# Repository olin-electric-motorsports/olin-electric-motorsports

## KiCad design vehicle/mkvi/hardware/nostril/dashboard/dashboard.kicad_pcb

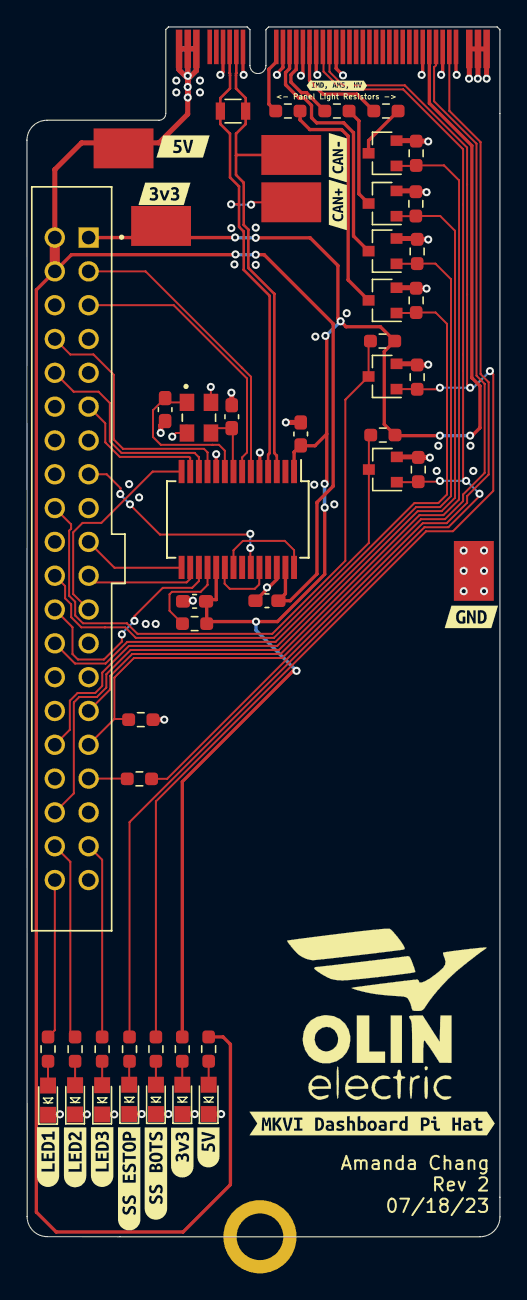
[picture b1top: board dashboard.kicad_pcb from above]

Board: 2 copper layers, 35.5 x 90.9 mm, 64 parts (0 on the bottom side), 48 nets.

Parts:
C4, C5, C6: C_0.1uF; C_0603_1608Metric_Pad1.08x0.95mm_HandSolder
C7, C8: C_14pF; C_0603_1608Metric_Pad1.08x0.95mm_HandSolder
D1, D7: LED_BLUE; LED_0805_OEM
D2, D3, D4, D5, D6: LED_0805; LED_0805_OEM
H1: M.2_MountingHole; M.2_Mount
J2: Automotive_M.2_Edge_Connector
J101: Conn_02x20_Odd_Even; SULLINS_SFH11-PBPC-D20-ST-BK
Q1, Q2, Q3, Q4, Q5, Q6: SSM3K333R; SOT-23F
R1, R7, R10, R16, R17, R18, R19, R20, R21: R_1K; R_0603_1608Metric_Pad0.98x0.95mm_HandSolder
R2, R12: R_100K; R_0603_1608Metric_Pad0.98x0.95mm_HandSolder
R3, R13, R14, R15: R_10K; R_0603_1608Metric_Pad0.98x0.95mm_HandSolder
R4, R5, R6, R8, R9, R11: R_200; R_0603_1608Metric_Pad0.98x0.95mm_HandSolder
R22: R_120_DNP; R_0805_OEM
TP1, TP2, TP3, TP4, TP5: Test_Point_SMD
U2: MCP25625-x-SS; SSOP-28_5.3x10.2mm_P0.65mm
Y1: Crystal_8MHz_12pF; XTAL_ECS-240-8-33-AGN-TR
kibuzzard-63A7A1A6: G***; kibuzzard-63A7A1A6
kibuzzard-63A7A1B1: G***; kibuzzard-63A7A1B1
kibuzzard-63A7A2B8: G***; kibuzzard-63A7A2B8
kibuzzard-63A7A2BB: G***; kibuzzard-63A7A2BB
kibuzzard-63A7A2C4: G***; kibuzzard-63A7A2C4
kibuzzard-63A7A2C6: G***; kibuzzard-63A7A2C6
kibuzzard-63A7A2C9: G***; kibuzzard-63A7A2C9
kibuzzard-63A7A2CE: G***; kibuzzard-63A7A2CE
kibuzzard-63A7A2D2: G***; kibuzzard-63A7A2D2
kibuzzard-63B4F55C: G***; kibuzzard-63B4F55C
kibuzzard-63B4F247: G***; kibuzzard-63B4F247
kibuzzard-63B43D68: G***; kibuzzard-63B43D68
kibuzzard-63B49D83: G***; kibuzzard-63B49D83
kibuzzard-63B49DDB: G***; kibuzzard-63B49DDB

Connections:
+3V3: C4.1, C5.1, J2.33, J101.1, R3.1, R5.1, R13.2, R14.1, TP3.1, U2.1 (VIO), U2.19 (VDD)
+5V: C6.2, J2.P1, J2.P2, J2.P3, J101.2, J101.4, R4.1, TP2.1, U2.27 (VDDA)
/AMS_LED_LOW_SIDE: J2.13, R20.1
/AMS_LED_LSD: J101.36, Q3.1 (G), R16.1
/BOTS_SHDN_SENSE: J101.18, Q6.3 (D), R3.2
/CAN_+: J2.7, R22.1, TP4.1, U2.4 (CANH)
/CAN_-: J2.8, R22.2, TP5.1, U2.3 (CANL)
/E_STOP_SHDN_SENSE: J101.22, Q1.3 (D), R14.2
/HV_LED_LOW_SIDE: J2.15, R21.1
/HV_LED_LSD: J101.29, Q5.1 (G), R18.1
/IMD_LED_LOW_SIDE: J2.10, R19.1
/IMD_LED_LSD: J101.26, Q2.1 (G), R10.1
/MCP25625 Chip/RX_CAN: U2.21 (RxCAN), U2.28 (RXD)
/MCP25625 Chip/TX_CAN: U2.20 (TxCAN), U2.24 (TXD)
/MCP25625 Chip/~INT: J101.11, U2.13 (~INT)
/MCP25625 Chip/~RESET: R13.1, U2.18 (~RESET)
/MCP25625 Chip/~TX1RTS: J101.3, U2.6 (~Tx1RTS)
/MCP25625 Chip/~TX2RTS: J101.5, U2.7 (~Tx2RTS)
/MISO: J101.21, U2.16 (SO)
/MOSI: J101.19, U2.15 (SI)
/PROGRAMMING_LED_1: J101.40, R6.1
/PROGRAMMING_LED_2: J101.38, R8.1
/PROGRAMMING_LED_3: J101.37, R9.1
/RTD_BUTTON_LED+: J101.33, R11.1
/RTD_BUTTON_SENSE-: J2.34, J101.31, R15.1
/RTD_BUZZER_LOW_SIDE: J2.12, Q4.3 (D)
/RTD_BUZZER_LSD: J101.32, Q4.1 (G), R17.1
/SCK: J101.23, U2.14 (SCK)
/SS_BOTS: J2.18, Q6.1 (G), R1.1, R2.1
/SS_ESTOP_DRIVER: J2.17, Q1.1 (G), R7.1, R12.1
/~CS: J101.24, U2.17 (~CS)
/~RX0BF: J101.10, U2.12 (~Rx0BF)
/~RX1BF: J101.8, U2.11 (~Rx1BF)
/~TX0RTS: J101.15, U2.23 (~Tx0RTS)
GND: C4.2, C5.2, C6.1, C7.2, C8.2, D1.1 (K), D2.1 (K), D3.1 (K), D4.1 (K), D5.1 (K), D6.1 (K), D7.1 (K), H1.1, J2.6, J2.9, J2.11, J2.14, J2.16, J2.19, J2.32, J2.35, J2.37, J2.P38, J2.P39, J2.P40, J101.6, J101.9, J101.14, J101.20, J101.25, J101.30, J101.34, J101.39, Q1.2 (S), Q2.2 (S), Q3.2 (S), Q4.2 (S), Q5.2 (S), Q6.2 (S), R2.2, R10.2, R12.2, R15.2, R16.2, R17.2, R18.2, TP1.1, U2.5 (STBY), U2.10 (GND), U2.26 (VSS), Y1.2, Y1.4
unnamed: D1.2 (A), R1.2
unnamed: D2.2 (A), R4.2
unnamed: D3.2 (A), R5.2
unnamed: D4.2 (A), R6.2
unnamed: D5.2 (A), R8.2
unnamed: D6.2 (A), R9.2
unnamed: D7.2 (A), R7.2
unnamed: J2.36, R11.2
unnamed: Q2.3 (D), R19.2
unnamed: Q3.3 (D), R20.2
unnamed: Q5.3 (D), R21.2
unnamed: C7.1, U2.9 (OSC1), Y1.1
unnamed: C8.1, U2.8 (OSC2), Y1.3

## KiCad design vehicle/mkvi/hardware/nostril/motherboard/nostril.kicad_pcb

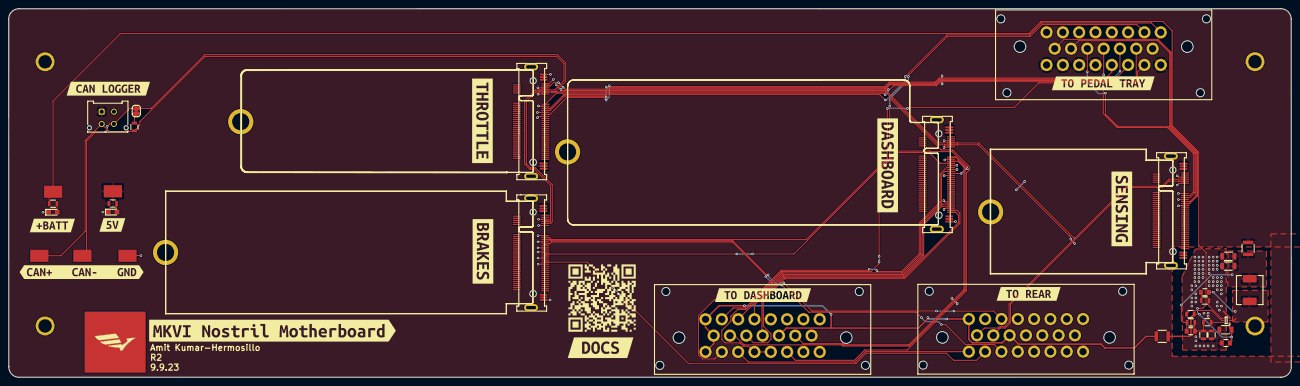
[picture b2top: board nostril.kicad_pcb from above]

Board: 2 copper layers, 314.4 x 90.3 mm, 53 parts (0 on the bottom side), 40 nets.

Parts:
C1: C_0.1uF; C_0805_OEM
C2, C5, C6: C_22uF; C_1206_OEM
C3: C_1uF; C_0805_OEM
C4: 15pF; C_0805_OEM
D1, D2: LED_WHITE; CHIPLED_0805
F1, F2: F_500mA_16V; Fuse_1210
J1, J2, J3: Ampseal_23_RA
J4, J5, J6, J7: Automotive_M.2
J8: MicroFit_VT_4
JP1: SolderJumper_2_Open; SolderJumper-2_P1.3mm_Open_RoundedPad1.0x1.5mm
L1: 2.2uH; IND_SPM6530T-2R2M
QR*****: https://coda.io/d/Documentation_dbuFnC2EA_e/Low-V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; __coda.io_d_Documentation_dbuFnC2EA_e_Low-Voltage-Syste
R1, R8: R_200; R_0805_OEM
R2: R_100K; R_0805_OEM
R3: 10R; R_0805_OEM
R4: R_75k; R_0805_OEM
R5: R_10K; R_0805_OEM
R6: R_33.2k; R_0805_OEM
R7: 40.2K; R_0805_OEM
R9: R_120_DNP; R_0805_OEM
REFe: MountingHole_440_Keystone_4939
REFe#2, REFe#3, REFe#4: MountingHole_440_Keystone_4939
TP1, TP2, TP3, TP4, TP5: Test_Point_SMD
U1: MP1477HGTF-P; SOTFL50P160X60-6N
kibuzzard-63FE4A40: G***; kibuzzard-63FE4A40
kibuzzard-63FE5D89: G***; kibuzzard-63FE5D89
kibuzzard-63FE5E2A: G***; kibuzzard-63FE5E2A
kibuzzard-63FE5E61: G***; kibuzzard-63FE5E61
kibuzzard-63FE5E77: G***; kibuzzard-63FE5E77
kibuzzard-63FE47A2: G***; kibuzzard-63FE47A2
kibuzzard-63FE47AC: G***; kibuzzard-63FE47AC
kibuzzard-63FE478D: G***; kibuzzard-63FE478D
kibuzzard-63FE479B: G***; kibuzzard-63FE479B
kibuzzard-63FE2233: G***; kibuzzard-63FE2233
kibuzzard-63FE2239: G***; kibuzzard-63FE2239
kibuzzard-63FE2383: G***; kibuzzard-63FE2383
kibuzzard-63FF646A: G***; kibuzzard-63FF646A

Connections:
+5V: F2.2, J3.1, J3.5, J3.6, J3.7, J3.8, J4.P1, J4.P2, J4.P3, J5.P38, J5.P39, J5.P40, J6.P1, J6.P2, J6.P3, J7.P1, J8.1, R8.2, TP4.1
+BATT: F1.1, J1.1, J1.9, J1.13, J1.16, J2.1, J2.11
/5V Buck/BUCK_EN: R2.2, U1.5 (EN)
/AMS_LED-: J1.2, J4.13
/BRAKELIGHT-: J2.18, J6.14, J6.15
/BRAKE_PRESSURE_SENSE: J3.2, J6.11
/CAN_+: J2.9, J4.7, J5.7, J6.7, J7.7, J8.3, R9.1, TP1.1
/CAN_-: J2.10, J4.8, J5.8, J6.8, J7.8, J8.4, JP1.2 (B), TP2.1
/IMD_LED-: J1.10, J4.10
/INPUT_THROTTLE_1: J3.10, J5.10
/INPUT_THROTTLE_2: J3.11, J5.5
/MOTOR_CURRENT_SENSE: J2.3, J6.12
/RTD_BUTTON_SENSE+: J1.3, J4.33
/RTD_BUTTON_SENSE-: J1.4, J4.34
/RTD_BUZZER-: J1.14, J4.12
/RTD_LED+: J1.11, J4.36
/RTD_LED-: J1.12, J4.37
/SHDN_BOTS_IN: J3.17, J4.18, J6.19, J6.20
/SHDN_BOTS_OUT: J1.21, J3.16, J5.12
/SHDN_ESTOP_IN: J1.19, J1.20, J4.17
/SHDN_ESTOP_OUT: J1.18, J2.16
/SHDN_OUT: J2.17, J6.22, J6.23
/SUS_TRAVEL_L_SIG: J3.14, J7.14
/SUS_TRAVEL_R_SIG: J3.15, J7.15
/THROTTLE_1+: J3.3, J5.13
/THROTTLE_2+: J3.4, J5.15
/TS_LED-: J1.17, J4.15
/WHEEL_SPEED_L_SIG: J3.12, J7.11
/WHEEL_SPEED_R_SIG: J3.13, J7.12
GND: C1.2, C2.2, C5.2, C6.2, D1.1 (K), D2.1 (K), J2.2, J3.9, J3.18, J3.19, J3.20, J3.21, J3.22, J3.23, J4.6, J4.9, J4.11, J4.14, J4.16, J4.19, J4.32, J4.35, J4.P38, J4.P39, J4.P40, J5.4, J5.6, J5.9, J5.11, J5.14, J5.16, J5.P1, J5.P2, J5.P3, J6.6, J6.9, J6.10, J6.13, J6.16, J6.18, J6.21, J6.24, J6.P38, J6.P39, J6.P40, J7.6, J7.9, J7.10, J7.13, J7.16, J8.2, R5.2, R6.2, REFe.1, REFe#2.1, REFe#3.1, REFe#4.1, TP5.1, U1.3 (GND)
unnamed: C3.1, R3.2
unnamed: C4.1, R4.2, R5.1, R6.1, R7.1
unnamed: C4.2, C5.1, C6.1, F2.1, L1.2, R7.2
unnamed: D1.2 (A), R1.1
unnamed: D2.2 (A), R8.1
unnamed: JP1.1 (A), R9.2
unnamed: R3.1, U1.4 (BST)
unnamed: R4.1, U1.6 (FB)
unnamed: C3.2, L1.1, U1.2 (SW)
unnamed: C1.1, C2.1, F1.2, R1.2, R2.1, TP3.1, U1.1 (VIN)

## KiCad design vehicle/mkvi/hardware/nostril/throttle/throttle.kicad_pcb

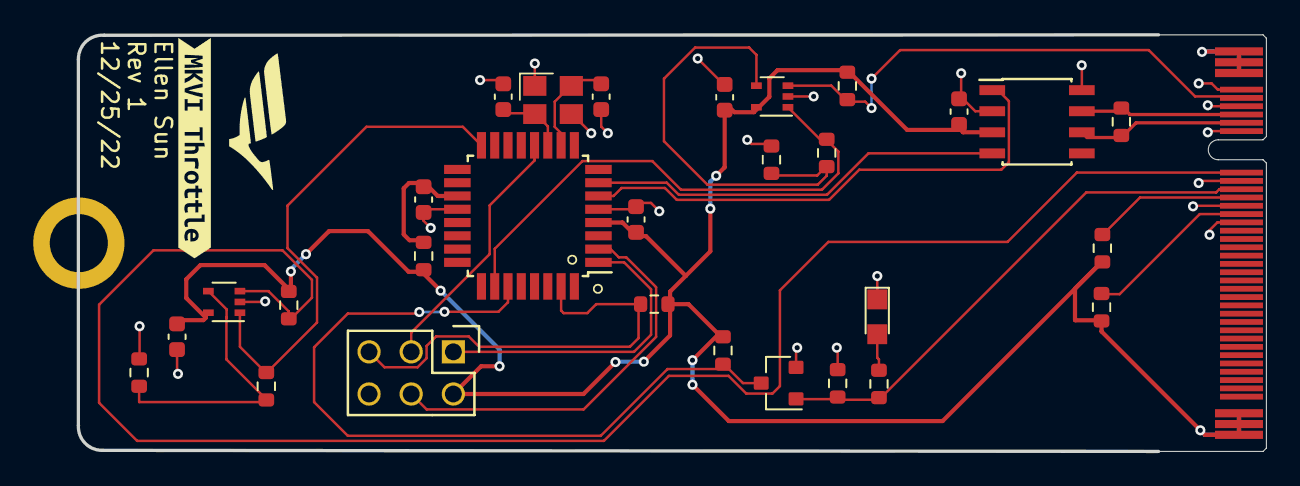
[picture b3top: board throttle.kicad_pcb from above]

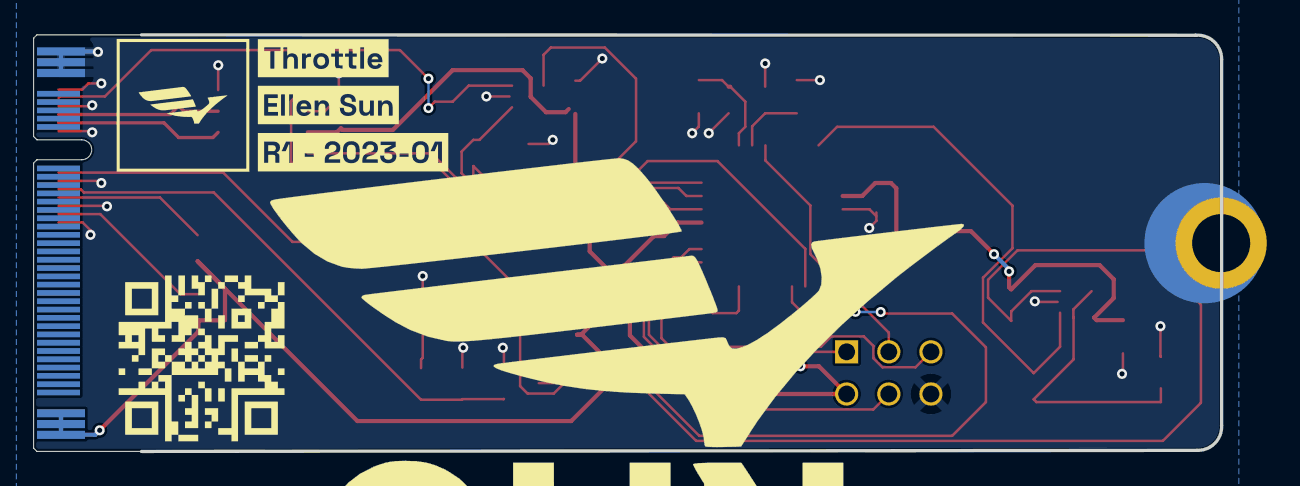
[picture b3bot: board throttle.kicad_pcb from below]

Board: 2 copper layers, 71.6 x 25.1 mm, 36 parts (4 on the bottom side), 24 nets.

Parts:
C1, C2, C3, C7: 0.1uF; C_0603
C4: C_100pF; C_0603
C5, C6: C_30pF; C_0603
D1: LED_BLUE; CHIPLED_0805
J1: Automotive_M.2_Edge_Connector
J2: CONN_02x03; Pin_Header_Straight_2x03
Q1: SSM3K333R; SOT-23F
QR*****: hw.oem.to/6_THROTTLE_1; QR_6_THROTTLE_1
R1, R4: R_1M; R_0603
R2, R5, R10, R11: R_0; R_0603
R3, R6: R_2.2K; R_0603
R7: 3KR; R_0603
R8: R_100K; R_0603
R9, R13: R_10K; R_0603
R12: R_100; R_0603
R14: R_120_DNP; R_0603
U1, U2: MCP6001; SOT-353_SC-70-5
U3: ATMEGA16M1; TQFP-32_7x7mm_Pitch0.8mm
U4: MAX33011EASA; SOIC-8_3.9x4.9mm_Pitch1.27mm_OEM
U$2: M.2_Mount
Y1: Crystal_16MHz_18pF; Crystal_TXC7M
kibuzzard-63A88E8E: G***; kibuzzard-63A88E8E
kibuzzard-63BF4696: G***; kibuzzard-63BF4696
kibuzzard-63D83A03: G***; kibuzzard-63D83A03
kibuzzard-63D83A10: G***; kibuzzard-63D83A10

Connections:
+5V: C1.1, C2.1, C3.1, C7.1, J1.P38, J1.P39, J1.P40, J2.2, R1.1, R4.1, R9.1, R10.1, R11.1, R12.1, R13.1, U1.5 (V+), U2.5 (V+), U3.4 (VCC), U4.3 (VDD)
/ Shutdown Sense Inertial Switch/SS_INERTIA_OUTPUT: Q1.3 (D), R9.2, U3.27 ((PCINT6/ADC7/PSCOUT1B)PB6)
/CAN_+: J1.7, R14.1, U4.7 (CANH)
/CAN_-: J1.8, R14.2, U4.6 (CANL)
/INPUT_THROTTLE_1: J1.10, R1.2, U1.3 (+)
/INPUT_THROTTLE_2: J1.5, R4.2, U2.3 (+)
/Microcontroller/CAN_RX: U3.7 ((PCINT11/T1/ICP1B/RXCAN)PC3), U4.4 (RXD)
/Microcontroller/CAN_TX: U3.6 ((PCINT10/T0/TXCAN)PC2), U4.1 (TXD)
/Microcontroller/MISO: J2.1, U3.1 ((PCINT18/PSCIN2/OC1A/MISO_A)PD2)
/Microcontroller/MOSI: J2.4, U3.2 ((PCINT19/TXD/TXLIN/OC0A/~SS/MOSI_A)PD3)
/Microcontroller/OUTPUT_THROTTLE_1: R2.1, U1.1, U3.16 ((PCINT2/ADC5/INT1/ACMPN0)PB2)
/Microcontroller/OUTPUT_THROTTLE_2: R5.1, U2.1, U3.26 ((PCINT5/ADC6/INT2/ACMPN1/AMP2-)PB5)
/Microcontroller/RESET: J2.5, R13.2, U3.31 ((PCINT24/OCD/~RESET)PE0)
/Microcontroller/SCK: J2.3, U3.12 ((PCINT20/ADC1/RXD/RXLIN/ICP1A/SCK_A)PD4)
/SS_INERTIA_SWITCH: J1.12, Q1.1 (G), R7.2, R8.1
/THROTTLE_1+: J1.13, R10.2
/THROTTLE_2+: J1.15, R11.2
GND: C1.2, C2.2, C3.2, C4.2, C5.2, C6.2, C7.2, D1.1 (K), J1.4, J1.6, J1.9, J1.11, J1.14, J1.16, J1.P1, J1.P2, J1.P3, J2.6, Q1.2 (S), R3.2, R6.2, R8.2, U1.2 (V-), U2.2 (V-), U3.5 (GND), U3.20 (AGND), U4.2 (VSS), U4.8 (STBY), U$2.1, Y1.2, Y1.4
unnamed: C4.1, R12.2, U3.19 (AVCC)
unnamed: C5.1, U3.11 ((PCINT26/ADC0/XTAL2)PE2), Y1.1
unnamed: C6.1, U3.10 ((PCINT25/OC0B/XTAL1)PE1), Y1.3
unnamed: D1.2 (A), R7.1
unnamed: R2.2, R3.1, U1.4 (-)
unnamed: R5.2, R6.1, U2.4 (-)

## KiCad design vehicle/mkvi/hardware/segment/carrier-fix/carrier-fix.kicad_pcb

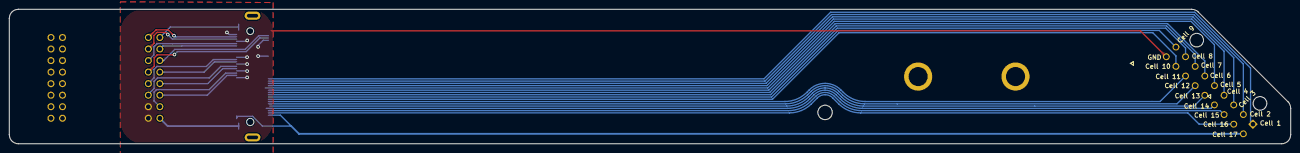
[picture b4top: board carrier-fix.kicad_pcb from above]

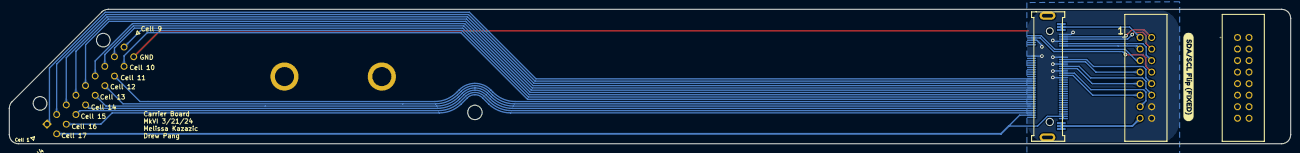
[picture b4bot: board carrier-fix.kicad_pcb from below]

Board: 2 copper layers, 282.1 x 29.6 mm, 6 parts (6 on the bottom side), 32 nets.

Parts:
J1: Automotive_M.2; MKVI_BMS_CSC
J2, J3: TST-108-01-T-D; TST-108-XX-T-D
J4, J4#2: MicroFit_RA_9x2
kibuzzard-65FD0D90: G***; kibuzzard-65FD0D90

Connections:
/CELL1: J1.56, J4.1
/CELL2: J1.57, J4.2
/CELL3: J1.58, J4.3
/CELL4: J1.59, J4.4
/CELL5: J1.60, J4.5
/CELL6: J1.61, J4.6
/CELL7: J1.62, J4.7
/CELL8: J1.63, J4.8
/CELL9: J1.64, J4.9
/CELL10: J1.65, J4.17
/CELL11: J1.66, J4.16
/CELL12: J1.67, J4.15
/CELL13: J1.68, J4.14
/CELL14: J1.69, J4.13
/CELL15: J1.70, J4.12
/CELL16: J1.71, J4.11
/CELL17: J1.36, J1.37, J1.72, J4.10
/GND: J1.4, J1.7, J1.10, J1.13, J1.16, J1.19, J1.43, J1.46, J2.14, J2.16, J4.18
/MUX1_SC: J1.18, J2.11
/MUX1_SD: J1.17, J2.13
/MUX2_SC: J1.15, J2.9
/MUX2_SD: J1.14, J2.12
/MUX3_SC: J1.12, J2.7
/MUX3_SD: J1.11, J2.10
/MUX4_SC: J1.9, J2.3
/MUX4_SD: J1.8, J2.6
/MUX_OUT_1: J1.6, J2.4
/MUX_OUT_2: J1.42, J2.8
/MUX_OUT_3: J1.5, J2.2
/MUX_OUT_4: J1.41, J2.5
/VREF2: J1.P38, J1.P39, J1.P40, J2.15
/VREG: J1.P1, J1.P2, J1.P3, J2.1

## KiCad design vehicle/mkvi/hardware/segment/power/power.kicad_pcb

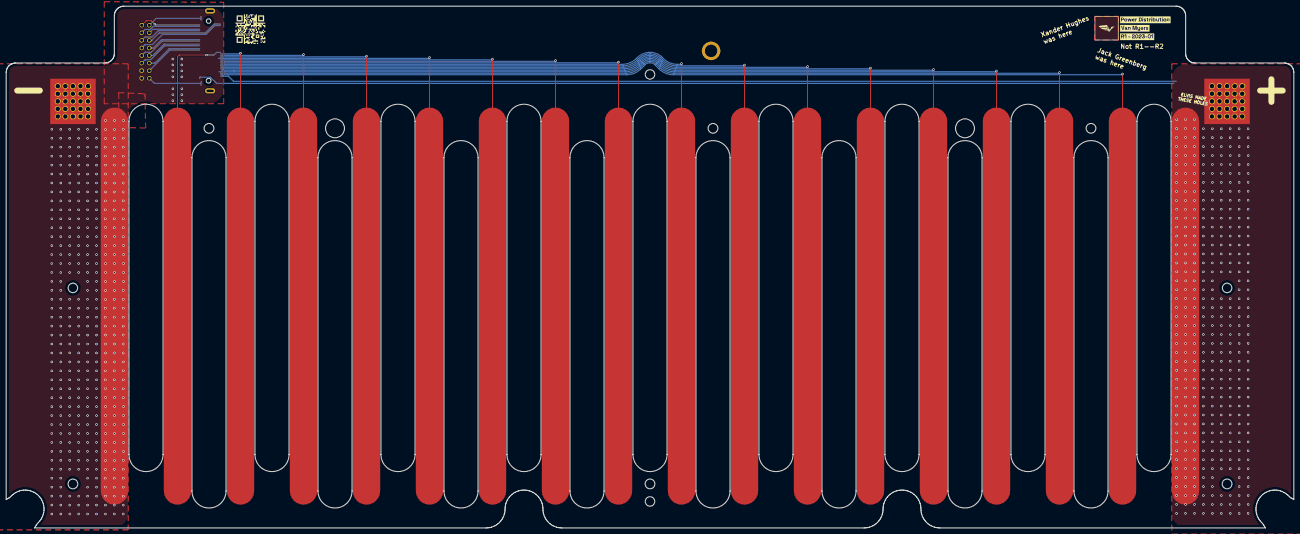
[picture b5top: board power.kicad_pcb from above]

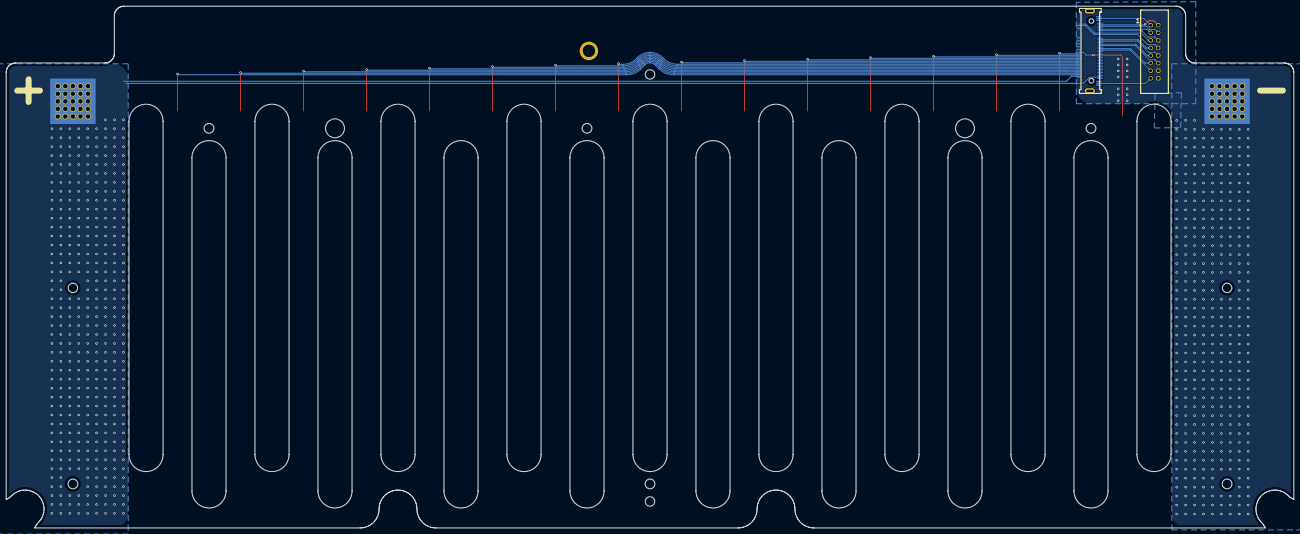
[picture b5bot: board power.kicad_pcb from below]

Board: 4 copper layers, 431.8 x 175.0 mm, 26 parts (4 on the bottom side), 32 nets.

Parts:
J1: Automotive_M.2; MKVI_BMS_CSC
J2: TST-108-01-T-D; TST-108-XX-T-D
QR*****: hw.oem.to/6_PD_1; QR_6_PD_1
TP1, TP2, TP3, TP4, TP5, TP6, TP7, TP8, TP9, TP10, TP11, TP12, TP13, TP14, TP15, TP16, TP17, TP18: TestPoint; Bond Pad
TP19, TP20: TestPoint; Wurth-7461115
kibuzzard-63B8B2B4: G***; kibuzzard-63B8B2B4
kibuzzard-63B8B2E9: G***; kibuzzard-63B8B2E9
kibuzzard-63BE1F6F: G***; kibuzzard-63BE1F6F

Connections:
/CELL1: J1.56, TP1.1
/CELL2: J1.57, TP2.1
/CELL3: J1.58, TP3.1
/CELL4: J1.59, TP4.1
/CELL5: J1.60, TP5.1
/CELL6: J1.61, TP6.1
/CELL7: J1.62, TP7.1
/CELL8: J1.63, TP8.1
/CELL9: J1.64, TP9.1
/CELL10: J1.65, TP10.1
/CELL11: J1.66, TP11.1
/CELL12: J1.67, TP12.1
/CELL13: J1.68, TP13.1
/CELL14: J1.69, TP14.1
/CELL15: J1.70, TP15.1
/CELL16: J1.71, TP16.1
/CELL17: J1.36, J1.37, J1.72, TP17.1, TP20.1
/MUX1_SC: J1.17, J2.11
/MUX1_SD: J1.18, J2.13
/MUX2_SC: J1.14, J2.9
/MUX2_SD: J1.15, J2.12
/MUX3_SC: J1.11, J2.7
/MUX3_SD: J1.12, J2.10
/MUX4_SC: J1.8, J2.3
/MUX4_SD: J1.9, J2.6
/MUX_OUT_1: J1.6, J2.4
/MUX_OUT_2: J1.42, J2.8
/MUX_OUT_3: J1.5, J2.2
/MUX_OUT_4: J1.41, J2.5
/VREF2: J1.P38, J1.P39, J1.P40, J2.15
/VREG: J1.P1, J1.P2, J1.P3, J2.1
GND: J1.4, J1.7, J1.10, J1.13, J1.16, J1.19, J1.43, J1.46, J2.14, J2.16, TP18.1, TP19.1

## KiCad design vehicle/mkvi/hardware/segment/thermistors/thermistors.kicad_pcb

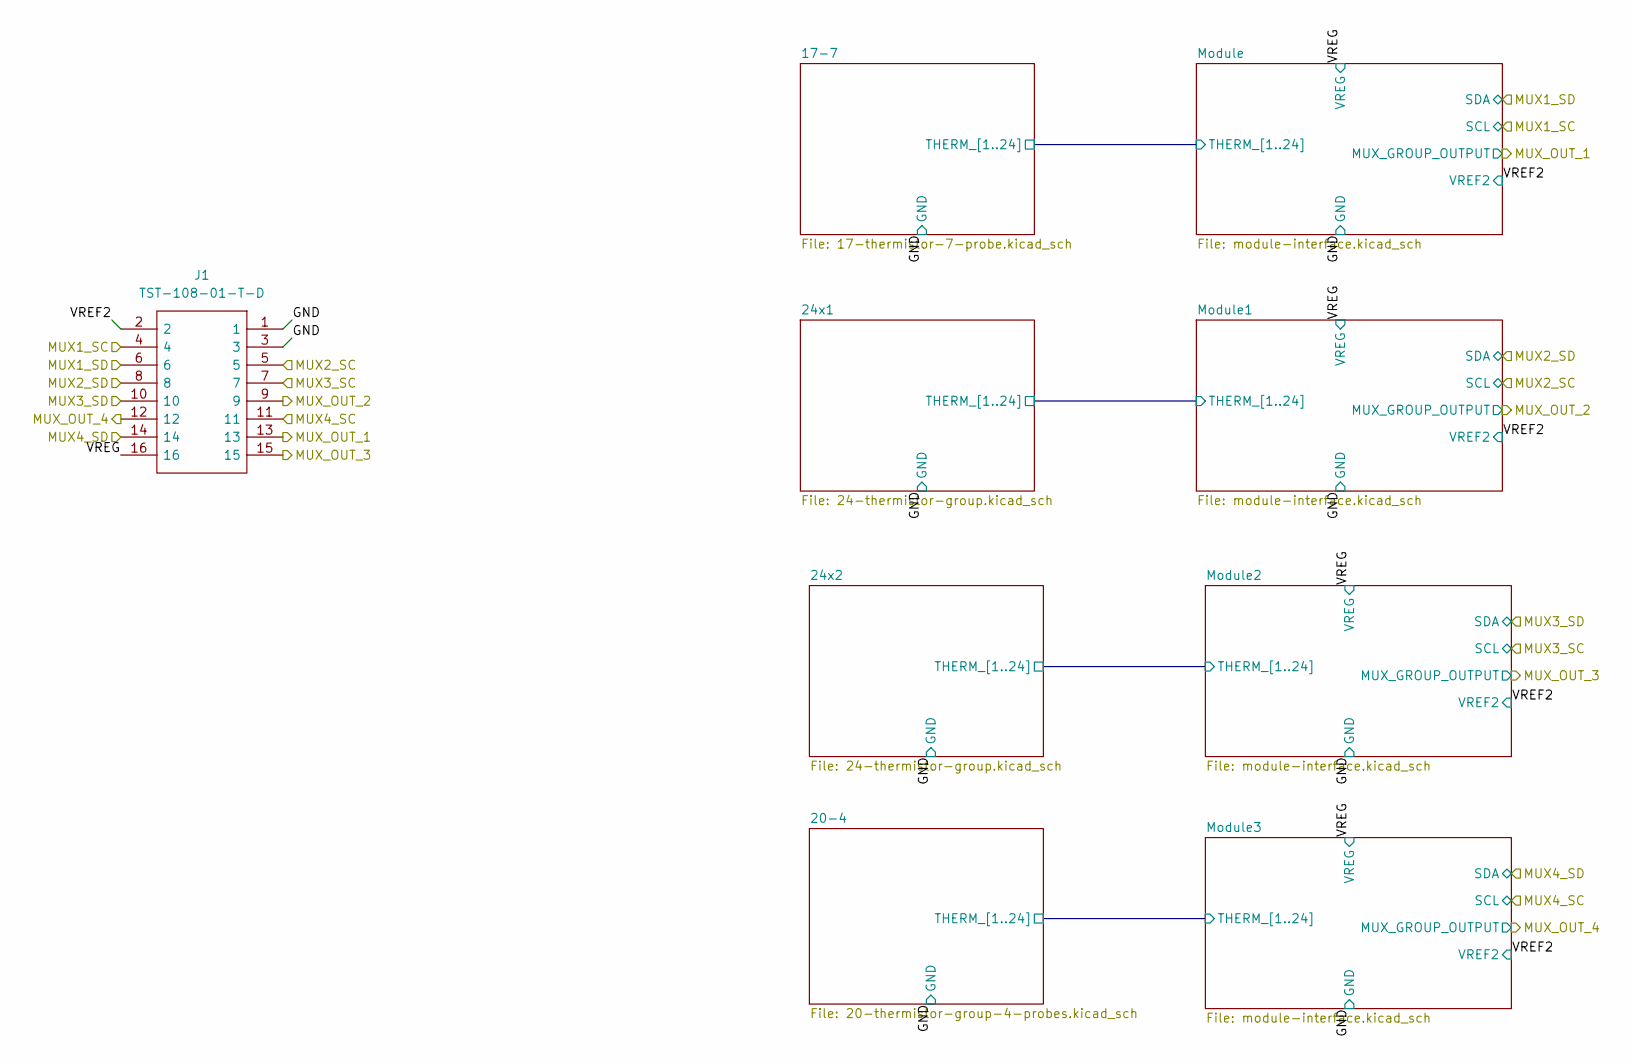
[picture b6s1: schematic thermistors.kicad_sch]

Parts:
J1: TST-108-01-T-D; TST-108-XX-T-D; MPN TST-108-01-T-D

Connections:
/GND: J1.1, J1.3; also elsewhere on the board
/MUX1_SC: J1.4; also elsewhere on the board
/MUX1_SD: J1.6; also elsewhere on the board
/MUX2_SC: J1.5; also elsewhere on the board
/MUX2_SD: J1.8; also elsewhere on the board
/MUX3_SC: J1.7; also elsewhere on the board
/MUX3_SD: J1.10; also elsewhere on the board
/MUX4_SC: J1.11; also elsewhere on the board
/MUX4_SD: J1.14; also elsewhere on the board
/MUX_OUT_1: J1.13; also elsewhere on the board
/MUX_OUT_2: J1.9; also elsewhere on the board
/MUX_OUT_3: J1.15; also elsewhere on the board
/MUX_OUT_4: J1.12; also elsewhere on the board
/VREF2: J1.2; also elsewhere on the board
/VREG: J1.16; also elsewhere on the board

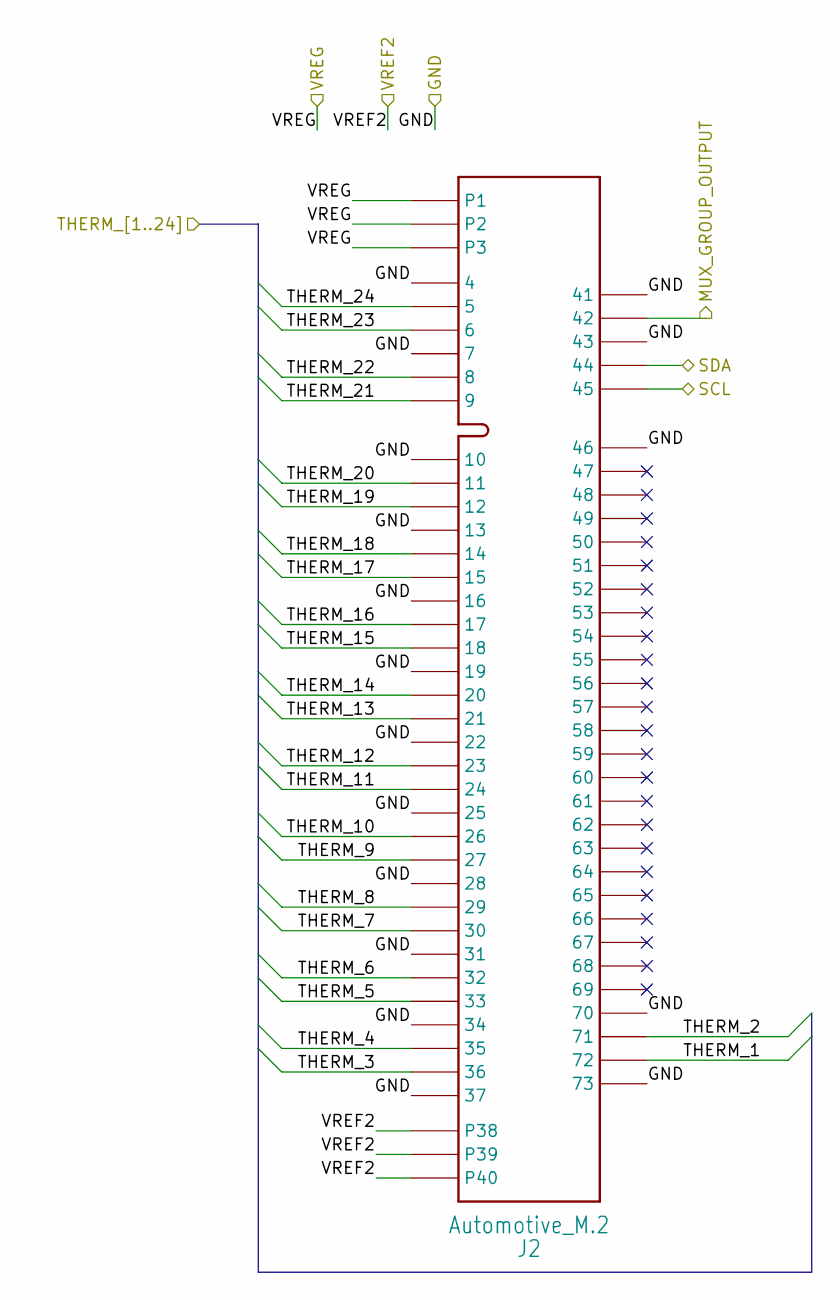
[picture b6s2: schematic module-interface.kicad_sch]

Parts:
J2: Automotive_M.2; MKVI_DA_Module; MPN CNU027S-067-2001-VE

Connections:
/17-7/THERM_1: J2.72; also elsewhere on the board
/17-7/THERM_2: J2.71; also elsewhere on the board
/17-7/THERM_3: J2.36; also elsewhere on the board
/17-7/THERM_4: J2.35; also elsewhere on the board
/17-7/THERM_5: J2.33; also elsewhere on the board
/17-7/THERM_6: J2.32; also elsewhere on the board
/17-7/THERM_7: J2.30; also elsewhere on the board
/17-7/THERM_8: J2.29; also elsewhere on the board
/17-7/THERM_9: J2.27; also elsewhere on the board
/17-7/THERM_10: J2.26; also elsewhere on the board
/17-7/THERM_11: J2.24; also elsewhere on the board
/17-7/THERM_12: J2.23; also elsewhere on the board
/17-7/THERM_13: J2.21; also elsewhere on the board
/17-7/THERM_14: J2.20; also elsewhere on the board
/17-7/THERM_15: J2.18; also elsewhere on the board
/17-7/THERM_16: J2.17; also elsewhere on the board
/17-7/THERM_17: J2.15; also elsewhere on the board
/17-7/THERM_18: J2.14; also elsewhere on the board
/17-7/THERM_19: J2.12; also elsewhere on the board
/17-7/THERM_20: J2.11; also elsewhere on the board
/17-7/THERM_21: J2.9; also elsewhere on the board
/17-7/THERM_22: J2.8; also elsewhere on the board
/17-7/THERM_23: J2.6; also elsewhere on the board
/17-7/THERM_24: J2.5; also elsewhere on the board
/GND: J2.4, J2.7, J2.10, J2.13, J2.16, J2.19, J2.22, J2.25, J2.28, J2.31, J2.34, J2.37, J2.41, J2.43, J2.46, J2.70, J2.73; also elsewhere on the board
/MUX1_SC: J2.44; also elsewhere on the board
/MUX1_SD: J2.45; also elsewhere on the board
/MUX_OUT_1: J2.42; also elsewhere on the board
/VREF2: J2.P38, J2.P39, J2.P40; also elsewhere on the board
/VREG: J2.P1, J2.P2, J2.P3; also elsewhere on the board

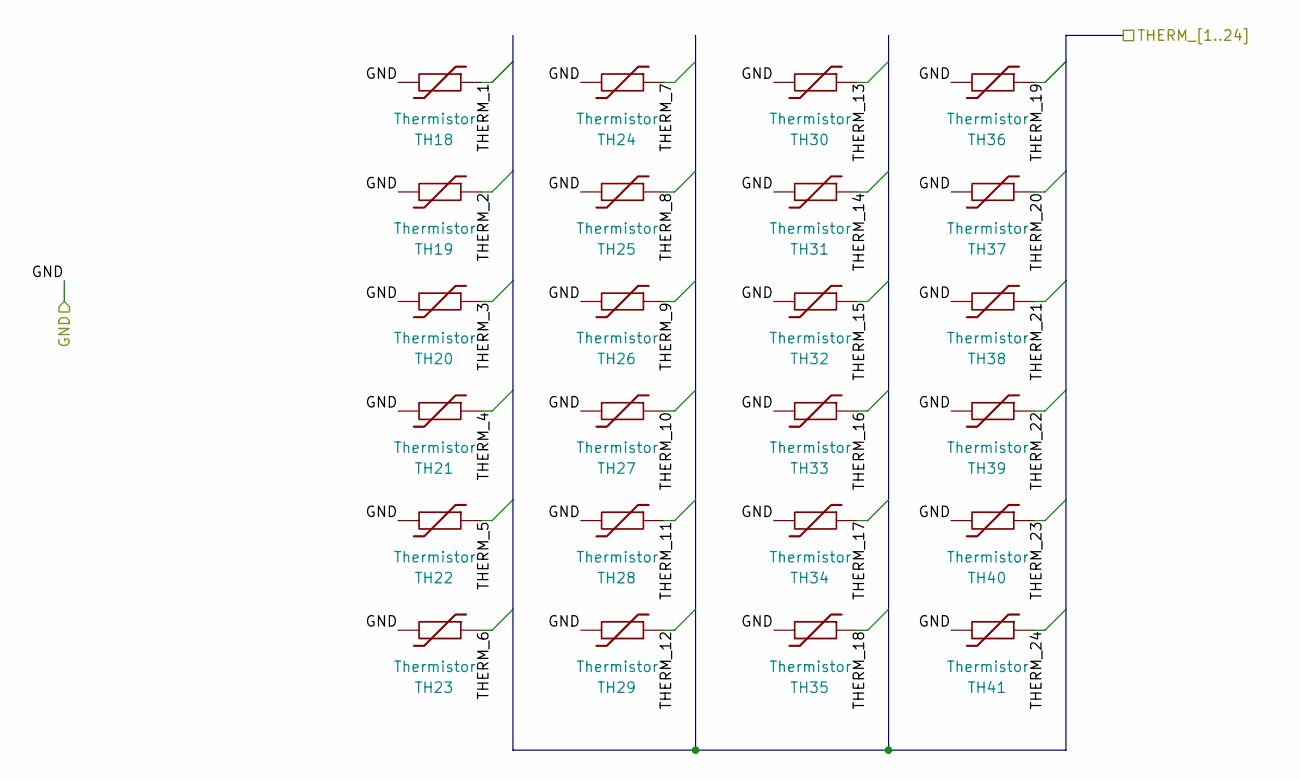
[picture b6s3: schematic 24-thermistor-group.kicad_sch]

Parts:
TH18, TH19, TH20, TH21, TH22, TH23, TH24, TH25, TH26, TH27, TH28, TH29, TH30, TH31, TH32, TH33, TH34, TH35, TH36, TH37, TH38, TH39, TH40, TH41: Thermistor; R_0603; MPN 273-TX06F104F4100ERDKR-ND

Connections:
/24x1/THERM_1: TH18.1; also elsewhere on the board
/24x1/THERM_2: TH19.1; also elsewhere on the board
/24x1/THERM_3: TH20.1; also elsewhere on the board
/24x1/THERM_4: TH21.1; also elsewhere on the board
/24x1/THERM_5: TH22.1; also elsewhere on the board
/24x1/THERM_6: TH23.1; also elsewhere on the board
/24x1/THERM_7: TH24.1; also elsewhere on the board
/24x1/THERM_8: TH25.1; also elsewhere on the board
/24x1/THERM_9: TH26.1; also elsewhere on the board
/24x1/THERM_10: TH27.1; also elsewhere on the board
/24x1/THERM_11: TH28.1; also elsewhere on the board
/24x1/THERM_12: TH29.1; also elsewhere on the board
/24x1/THERM_13: TH30.1; also elsewhere on the board
/24x1/THERM_14: TH31.1; also elsewhere on the board
/24x1/THERM_15: TH32.1; also elsewhere on the board
/24x1/THERM_16: TH33.1; also elsewhere on the board
/24x1/THERM_17: TH34.1; also elsewhere on the board
/24x1/THERM_18: TH35.1; also elsewhere on the board
/24x1/THERM_19: TH36.1; also elsewhere on the board
/24x1/THERM_20: TH37.1; also elsewhere on the board
/24x1/THERM_21: TH38.1; also elsewhere on the board
/24x1/THERM_22: TH39.1; also elsewhere on the board
/24x1/THERM_23: TH40.1; also elsewhere on the board
/24x1/THERM_24: TH41.1; also elsewhere on the board
/GND: TH18.2, TH19.2, TH20.2, TH21.2, TH22.2, TH23.2, TH24.2, TH25.2, TH26.2, TH27.2, TH28.2, TH29.2, TH30.2, TH31.2, TH32.2, TH33.2, TH34.2, TH35.2, TH36.2, TH37.2, TH38.2, TH39.2, TH40.2, TH41.2; also elsewhere on the board

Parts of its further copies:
TH42, TH43, TH44, TH45, TH46, TH47, TH48, TH49, TH50, TH51, TH52, TH53, TH54, TH55, TH56, TH57, TH58, TH59, TH60, TH61, TH62, TH63, TH64, TH65: Thermistor; R_0603; MPN 273-TX06F104F4100ERDKR-ND

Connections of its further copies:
/24x2/THERM_1: TH42.1; also elsewhere on the board
/24x2/THERM_2: TH43.1; also elsewhere on the board
/24x2/THERM_3: TH44.1; also elsewhere on the board
/24x2/THERM_4: TH45.1; also elsewhere on the board
/24x2/THERM_5: TH46.1; also elsewhere on the board
/24x2/THERM_6: TH47.1; also elsewhere on the board
/24x2/THERM_7: TH48.1; also elsewhere on the board
/24x2/THERM_8: TH49.1; also elsewhere on the board
/24x2/THERM_9: TH50.1; also elsewhere on the board
/24x2/THERM_10: TH51.1; also elsewhere on the board
/24x2/THERM_11: TH52.1; also elsewhere on the board
/24x2/THERM_12: TH53.1; also elsewhere on the board
/24x2/THERM_13: TH54.1; also elsewhere on the board
/24x2/THERM_14: TH55.1; also elsewhere on the board
/24x2/THERM_15: TH56.1; also elsewhere on the board
/24x2/THERM_16: TH57.1; also elsewhere on the board
/24x2/THERM_17: TH58.1; also elsewhere on the board
/24x2/THERM_18: TH59.1; also elsewhere on the board
/24x2/THERM_19: TH60.1; also elsewhere on the board
/24x2/THERM_20: TH61.1; also elsewhere on the board
/24x2/THERM_21: TH62.1; also elsewhere on the board
/24x2/THERM_22: TH63.1; also elsewhere on the board
/24x2/THERM_23: TH64.1; also elsewhere on the board
/24x2/THERM_24: TH65.1; also elsewhere on the board
/GND: TH42.2, TH43.2, TH44.2, TH45.2, TH46.2, TH47.2, TH48.2, TH49.2, TH50.2, TH51.2, TH52.2, TH53.2, TH54.2, TH55.2, TH56.2, TH57.2, TH58.2, TH59.2, TH60.2, TH61.2, TH62.2, TH63.2, TH64.2, TH65.2; also elsewhere on the board

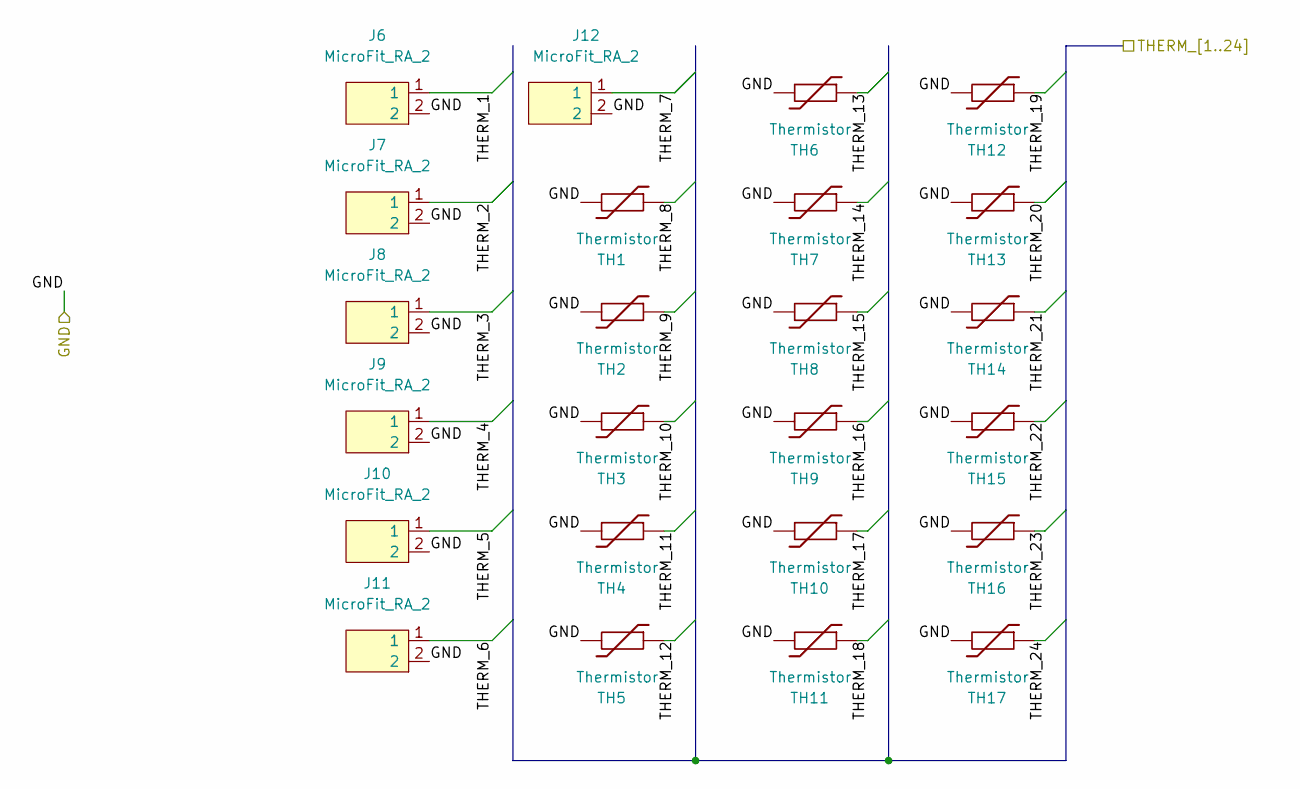
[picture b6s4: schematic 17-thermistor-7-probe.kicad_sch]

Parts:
J6, J7, J8, J9, J10, J11, J12: MicroFit_RA_2; MPN 0436500201
TH1, TH2, TH3, TH4, TH5, TH6, TH7, TH8, TH9, TH10, TH11, TH12, TH13, TH14, TH15, TH16, TH17: Thermistor; R_0603; MPN 273-TX06F104F4100ERDKR-ND

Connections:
/17-7/THERM_1: J6.1; also elsewhere on the board
/17-7/THERM_2: J7.1; also elsewhere on the board
/17-7/THERM_3: J8.1; also elsewhere on the board
/17-7/THERM_4: J9.1; also elsewhere on the board
/17-7/THERM_5: J10.1; also elsewhere on the board
/17-7/THERM_6: J11.1; also elsewhere on the board
/17-7/THERM_7: J12.1; also elsewhere on the board
/17-7/THERM_8: TH1.1; also elsewhere on the board
/17-7/THERM_9: TH2.1; also elsewhere on the board
/17-7/THERM_10: TH3.1; also elsewhere on the board
/17-7/THERM_11: TH4.1; also elsewhere on the board
/17-7/THERM_12: TH5.1; also elsewhere on the board
/17-7/THERM_13: TH6.1; also elsewhere on the board
/17-7/THERM_14: TH7.1; also elsewhere on the board
/17-7/THERM_15: TH8.1; also elsewhere on the board
/17-7/THERM_16: TH9.1; also elsewhere on the board
/17-7/THERM_17: TH10.1; also elsewhere on the board
/17-7/THERM_18: TH11.1; also elsewhere on the board
/17-7/THERM_19: TH12.1; also elsewhere on the board
/17-7/THERM_20: TH13.1; also elsewhere on the board
/17-7/THERM_21: TH14.1; also elsewhere on the board
/17-7/THERM_22: TH15.1; also elsewhere on the board
/17-7/THERM_23: TH16.1; also elsewhere on the board
/17-7/THERM_24: TH17.1; also elsewhere on the board
/GND: J6.2, J7.2, J8.2, J9.2, J10.2, J11.2, J12.2, TH1.2, TH2.2, TH3.2, TH4.2, TH5.2, TH6.2, TH7.2, TH8.2, TH9.2, TH10.2, TH11.2, TH12.2, TH13.2, TH14.2, TH15.2, TH16.2, TH17.2; also elsewhere on the board
